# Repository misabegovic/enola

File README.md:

> **This fork is the source of munola releases.** `munola` is a distribution
> of enola built from the `current` channel of misabegovic/mu-enola, carved
> into this repository's `munola-releases-<version>` lineage: the released
> upstream plus changes that are proposed upstream, under review, or that
> upstream may never take. Releases are cut from tags `munola-v<upstream
> version>.<n>` (for example `munola-v0.4.4.1` is the first munola release on
> upstream 0.4.4), carry the same asset names as upstream with that version,
> and their notes name exactly what differs from the upstream version they
> descend from. Everything below this line is upstream's README.

<div align="center">

  <h1>enola</h1>

  <p>enola - One graph of your whole software system, built from the code, on your machine</p>

  <p align="center">
  <a href="https://enola.tech">Website</a>
  ·
  <a href="docs/README.md">Docs</a>
  ·
  <a href="docs/CLI.md">CLI reference</a>
  ·
  <a href="docs/BENCHMARKS.md">Benchmarks</a>
  ·
  <a href="https://github.com/enola-labs/enola/releases">Releases</a>
  ·
  <a href="https://github.com/enola-labs/enola/issues">Report a gap</a>
  </p>

  <p>

  </p>

  <p>enola reads your source code and writes down what is in it: the modules, the functions, the API routes, the database tables it touches, the message topics it publishes. Then it records how each of those pieces connects to the others, inside one repository and across several. That record is a <em>graph</em>: a list of things, and a list of links between them. You can ask the graph questions, hand it to your coding agent, or build your own tools on it.</p>

  <p><strong>Runs locally as one binary. No AI model, no language server, no account, no upload.</strong><br />
  The graph comes from parsing your code. The same code always produces the same graph.</p>

</div>

## When to use enola

- **Find out what a change will break.** Before you edit a function, a route, or a module, ask the graph what depends on it. The answer is a list of real places in the code, not a guess. [Quickstart](#quickstart).
- **Keep your architecture the way you declared it.** Write down the layer order your code should follow, or which service may call which. Every change is then graded against that, and only what the change broke is reported. [Grade a change](#grade-a-change).
- **Give your coding agent the structure of the system.** Over MCP, the agent asks the graph what depends on the code it is about to touch, and a hook grades its edit when it is done. [Connect your agent](#connect-your-agent).
- **See several repositories as one system.** A frontend's call to `/api/orders` is linked to the Go handler that serves it. One service's Kafka producer is linked to the service that consumes the topic. [Across repositories](#across-repositories).
- **Build your own tools on the graph.** A snapshot is a set of plain files with a documented format. Load them wherever you need them. [Build on the graph](#build-on-the-graph).

That difference shows up in ordinary work. Across 238 real Claude Code and OpenCode sessions, 4,375 enola calls put 4.1 million tokens into context. Opening only the files named in those answers was estimated at 5.4× to 7.7× as much; reading the full source represented by each session, 450× to 623×. In 205 of 210 sessions that took a snapshot, that source was larger than the agent's median active context. [Measured latency, token costs, method and limits](docs/BENCHMARKS.md#real-session-usage).

## Choose your starting point

| I want to… | Start here |
| --- | --- |
| See what enola finds in a repository I have | [Quickstart](#quickstart) |
| Check whether a change broke the architecture | [Grade a change](#grade-a-change) |
| Run that check on every pull request | [Use it in CI](#use-it-in-ci) |
| Give my coding agent the graph | [Connect your agent](#connect-your-agent) |
| Link a backend and the apps that call it | [Across repositories](#across-repositories) |
| Load the graph into my own tool | [Build on the graph](#build-on-the-graph) |
| Know which languages it understands | [What it reads](#what-it-reads) |
| Follow one worked example end to end | [Your first graded change](docs/FIRST-CHANGE.md) |

## Quickstart

**1. Install enola.** One prebuilt binary; no Go toolchain or C compiler needed.

```bash
curl -fsSL https://raw.githubusercontent.com/enola-labs/enola/main/install.sh | sh
```

This puts `enola` in `~/.local/bin`. The same binary is on PyPI (`pip install enola-cli`) and RubyGems. Every install route, and how to upgrade, is in [docs/CLI.md](docs/CLI.md#install).

**2. Point it at a repository you have checked out.**

```bash
enola --explain /path/to/your/repo
```

No config file, no account, nothing written to disk. It reads the code and prints what it found. If you have nothing at hand, run it on enola itself:

```bash
git clone https://github.com/enola-labs/enola
enola --explain enola
```

Part of what that prints (the numbers move as the code does):

```
Overview
  Languages:           go, typescript, c, ruby, python
  Total facts:         10814

Architecture
  cyclic dependencies         0
  layer violations            0

Impact analysis (hotspots)
  Top hotspots (by coupling):
    module                            fan-in  fan-out crit     blast radius
    internal/facts                       253        1 high     96
    pkg/command                            1       94 high     1
    pkg/bootstrap                         15       69 high     4
```

How to read it:

- A **fact** is one thing enola recorded: "this function exists", "this function calls that one", "this route is served here". `Total facts` is how many it found.
- A **cyclic dependency** is two or more modules that each need the other, so neither can be changed or tested alone.
- A **layer violation** is a module reaching into a layer it is not allowed to use, under a layer order the repository declared. enola declares its own in [`enola-intent.yaml`](enola-intent.yaml); 0 means nothing in the code crosses it.
- A **hotspot** is a module many other modules depend on. `fan-in` is how many modules use it; `fan-out` is how many it uses; `blast radius` is how many modules a change to it can reach. Read the first row as: `internal/facts` is used from 253 places, and a change to it can reach 96 modules.

**3. Keep the graph and look at it.** `--explain` only prints. To save the graph, build it with `--generate`. It is written under `.enola/` in the repository, and that saved graph is what the local dashboard shows:

```bash
enola --generate .
enola dashboard --open
```

The dashboard is a local web page; nothing is sent anywhere. [Dashboard guide](docs/DASHBOARD.md).

## How enola works

enola parses each source file, turns what it finds into typed facts, links the facts into a graph, and runs checks over the graph: dependency cycles, layer violations, unused routes, hotspots and more. Each check is called an **explainer**, and [docs/EXPLAINERS.md](docs/EXPLAINERS.md) describes every one of them.

| Command | What it does | Learn more |
| --- | --- | --- |
| `enola --explain <repo>` | Read a repository and print a report. Writes nothing. | [CLI reference](docs/CLI.md#explain-a-repository-at-a-glance) |
| `enola --generate <repo>` | Build the graph and save it under `.enola/` as a snapshot. | [The graph](docs/GRAPH.md) |
| `enola baseline pin` | Record the current state of the graph as the point to compare against. | [Gating a change](docs/GATING.md) |
| `enola check` | Build the graph again and report only what changed since the pin. | [Gating a change](docs/GATING.md) |
| `enola coverage <cluster>` | For several repositories, say which cross-repository calls were linked and which could not be. | [Clusters](docs/CLUSTERS.md) |
| `enola dashboard --open` | Show the saved graph in a local web page. | [Dashboard guide](docs/DASHBOARD.md) |
| `enola install --hooks` | Tell your coding agents enola exists and grade each of their sessions. | [Connect your agent](#connect-your-agent) |

Three properties hold for all of it:

- **Deterministic.** The same code always gives the same graph. 91 open-source repositories indexed three times each (once cold, twice warm) gave byte-identical results, over 8.1 million facts. Every snapshot carries a **receipt**: a record of exactly how it was built. enola refuses to compare two snapshots that were not built the same way.
- **Fast enough for every commit.** Re-indexing an unchanged tree took 4.8s for grafana and 41.5s for the Linux kernel.
- **Local.** One binary reading local files. No model, no embeddings, no upload.

What the graph contains and what it writes to disk: [docs/GRAPH.md](docs/GRAPH.md). The numbers above and the scripts that produce them: [docs/BENCHMARKS.md](docs/BENCHMARKS.md). Internals: [ARCHITECTURE.md](ARCHITECTURE.md).

## Grade a change

The simplest way to see what changed is to check what came in with a pull. Record the current state, pull, and compare:

```bash
enola baseline pin
git pull
enola check
```

`enola check` builds the graph again and reports only what changed since the pin: new dependencies, new calls, new findings. Problems the repository already had stay out of the report. Your own edits work the same way: pin, change, check.

Here a new helper in `storage` imports the delivery layer. It compiles, every test passes, and it breaks the layer order the repository declared:

```
FAIL — 1 structural regression introduced.

Regressions (fail):
  - [layers] 1.00 — Layer violation: storage -> delivery
      import of notify
```

A **regression** is something the change made worse compared with the pin. Some checks grade against how you say your system should look, such as a layer order or which service may call which. You write that down in [docs/INTENT.md](docs/INTENT.md) and [docs/CONSTRAINTS.md](docs/CONSTRAINTS.md).

Nothing fails by default. You choose what should, for example `enola check --fail-on=layers`. [docs/GATING.md](docs/GATING.md) explains what can fail a build and why; [docs/HISTORY.md](docs/HISTORY.md) covers how the architecture changed over time. The whole loop on a module small enough to read in a minute: [docs/FIRST-CHANGE.md](docs/FIRST-CHANGE.md).

## Use it in CI

The same check runs on every pull request with [enola-action](https://github.com/enola-labs/enola-action). It resolves the exact base commit, grades both sides on the runner, annotates the lines that introduced a finding, and writes the architecture delta to the job summary:

```yaml
- uses: actions/checkout@v7
  with:
    fetch-depth: 0
- uses: enola-labs/enola-action@v2   # reports only; add fail-on to gate
```

Same explainers and same exit codes as `enola check` in your shell, with no baseline to publish or restore. A ready workflow file is in [`examples/ci/`](examples/ci/).

## Connect your agent

First tell your agents enola exists, and let it grade each session:

```bash
enola install --hooks
```

Then give the agent the graph over **MCP** (Model Context Protocol: the standard way a coding agent calls an outside tool):

| Client | Do this |
|---|---|
| **Claude Code** | `claude mcp add enola enola` |
| **Codex** | `codex mcp add enola -- enola` |
| **Copilot (VS Code)** | `code --add-mcp '{"name":"enola","command":"enola"}'` |
| **Cursor** | add the block below to `.cursor/mcp.json` (or `~/.cursor/mcp.json` for every project) |
| **opencode** | nothing, `enola install` already registered it |
| **Pi** | nothing, `enola install` wrote an extension that serves the tools (Pi has no MCP client); trust the project in Pi, or use `--global` |
| **Any other MCP client** | add the block below to its MCP config |

```json
{ "mcpServers": { "enola": { "command": "enola" } } }
```

What changes for the agent: before an edit, it asks the graph what depends on the code it is about to touch, instead of piecing that together from text searches. After the edit, a **hook** (a command the agent runs automatically at the end of its turn) runs the same `enola check` as above. The agent sees what it actually changed and fixes a regression before telling you it is done.

`enola install` previews every file it changes and asks first; `enola uninstall` reverses all of it. `enola doctor` tells you whether the hooks are really firing. Per-client details, including Copilot's different config key: [docs/CLI.md](docs/CLI.md#connect-it-to-your-agent).

## Across repositories

A system rarely lives in one repository, so enola does not stop at one. Give it a backend and the things that call it (a web app, a mobile app, another service) and it links them into one graph. Then it can answer: *if I change this endpoint, what breaks?*

The hard part is that two sides rarely spell an endpoint the same way. In [`examples/cross-repo/`](examples/cross-repo/) the web service calls `/api/v2/orders/{id}`, but the API service never writes that string anywhere:

```go
v2 := r.PathPrefix("/api/v2").Subrouter()
registerOrders(v2)                        // in main()

r.HandleFunc("/orders/{id}", getOrder)    // in registerOrders(), a different function
```

enola follows the prefix into the function it was passed to and files the route under the address it actually answers on, so the call links. It does the same for Express, FastAPI, Axum, Rails and Swift, where the prefix often sits in another file entirely.

When it *cannot* link something, it says so instead of guessing:

```
$ enola coverage cluster.yaml

  service  classification  detected  resolved  unresolved
  api      isolated              0         0           0
  web      connected             3         2           1
```

The unresolved call builds its URL at runtime, so there is nothing to match. That distinction matters: a service with no connections and a service whose connections enola failed to follow should never look the same. The example runs in one command: `./run.sh`. How several repositories are described and matched: [docs/CLUSTERS.md](docs/CLUSTERS.md).

## Build on the graph

A **snapshot** is a set of plain files with a [documented format](docs/schema/README.md): the facts, the relationships between them, the findings, and a receipt recording exactly how it was built. Run enola as a subprocess and load those files wherever you need them.

[Cognee](https://github.com/topoteretes/cognee) builds its code-graph search this way: it pins an `enola-cli` release and loads the snapshot files, and that search needs no LLM key. How it finds the binary and what it writes: [docs/INTEGRATING.md](docs/INTEGRATING.md#cognee). If you got enola as part of Cognee, [docs/COGNEE.md](docs/COGNEE.md) shows where the binary is and how to use it directly.

[docs/GRAPH.md](docs/GRAPH.md) explains what the graph contains and which files are a stable contract; [docs/INTEGRATING.md](docs/INTEGRATING.md) shows how to load it step by step.

## What it reads

More than twenty languages and formats, detected automatically. A repository with two languages is indexed as two languages without being told.

- **Application code:** Go, Java, Kotlin, Scala, JavaScript, TypeScript, Vue, Svelte, Ember, Angular, Python, Ruby, PHP, Swift, Dart/Flutter, Rust, C/C++, .NET (C#, VB.NET, F#)
- **APIs and messaging:** OpenAPI, gRPC, GraphQL, AsyncAPI
- **Infrastructure:** Terraform/HCL, Ansible

On top of the language it understands the frameworks that shape routes, storage and wiring, among them Rails, Django, FastAPI, Spring, Express, Next.js, ASP.NET Core, Laravel, Axum, SwiftUI and Jetpack Compose. The full table is in [docs/LANGUAGES.md](docs/LANGUAGES.md). A language you do not see there is a gap worth [reporting](https://github.com/enola-labs/enola/issues).

## Explore examples

Each example is a small repository plus a `run.sh` that reproduces the output shown in its README.

- [The gate on five packages](examples/layers-gate/): a module built to a layer order, and one change that breaks it. This is the fixture the outputs in this README come from.
- [Two repositories, one graph](examples/cross-repo/): a web service and the API it calls, with one call enola can link and one it reports as unresolved.
- [Policy as code](examples/policy-as-code/): PCI DSS and GDPR-inspired constraints on a small Go module, with three changes that violate them.
- [A custom HTTP client](examples/custom-client/): teaching enola an in-house client so its calls link to server routes.
- [A CI workflow](examples/ci/) and [a pre-commit hook](examples/hooks/) ready to copy.
- [Per-language configuration files](examples/) for Go, TypeScript, Python, Ruby, PHP, Kotlin, Swift and C++.

## Benchmarks

Every number below is measured on public repositories with scripts you can rerun. Method, corpus and limits: [docs/BENCHMARKS.md](docs/BENCHMARKS.md).

| Question | Result | What was measured |
| --- | --- | --- |
| Does the same commit produce the same graph? | **91 / 91** | public repositories produced byte-identical graphs across a cold run and two warm ones |
| When something regresses, is exactly that reported? | **20 / 20** | injected dependency cycles caught, with none of 1,859 pre-existing findings repeated as new |
| Of the cross-repository calls that exist, how many are linked? | **19 / 24** | fixture calls resolved, with the 3 unresolved and 2 external ones reported, not hidden |
| Does it finish on a real repository? | **0** | parse errors across the whole corpus, the Linux kernel included |
| Does an agent, given the check, avoid shipping the regression? | **3 / 3 → 0 / 3** | agents shipped the injected cycle without enola, and none did with the hooks installed |

## Limitations

- enola models structure, not runtime behaviour. It knows a service calls another; it knows nothing about timeouts, retries or whether a message can be lost.
- Calls it cannot resolve, such as URLs built at runtime, are reported as unresolved rather than guessed. Per-language limits are in [docs/extraction/](docs/extraction/) and the gaps found so far in [docs/BLIND-SPOTS.md](docs/BLIND-SPOTS.md).
- Most findings are advisory. Across the benchmark corpus, 89.2% of them could not fail a build even with every check named.
- A clean `enola check` means the change introduced nothing new, not that the repository is clean.

With a coding agent, most of these stop being dead ends. enola says exactly where its knowledge stops: which call it could not resolve, which finding is only advisory. The agent can open that file, read the retry settings or the URL being built, and judge whether a finding matters for this change. The graph shows the agent where to look; the agent reads what the graph cannot hold. What the agent concludes is still the agent's judgement, not a measurement, and enola keeps the two apart.

## Documentation

- **[Choose a guide by task](docs/README.md)**
- **[Your first graded change](docs/FIRST-CHANGE.md)**: the loop end to end, on a module small enough to read
- **[The graph](docs/GRAPH.md)**: what is in it, how it is built, what it writes to disk
- **[CLI reference](docs/CLI.md)**: install, agent setup, commands, flags and exit codes
- **[Gating a change](docs/GATING.md)**: what a verdict contains and what can fail a build
- **[Dashboard guide](docs/DASHBOARD.md)**
- **[Building on enola](docs/INTEGRATING.md)**
- **[Glossary](docs/GLOSSARY.md)**: the terms used in enola's output
- **[Architecture](ARCHITECTURE.md)**: the fact model, pipeline, graph and MCP tools
- **[Changelog](CHANGELOG.md)** and **[examples](examples/)**

## Community & Support

### Found it useful?

If `enola --explain` told you something about your codebase you did not already know, a star helps other people find it.

If it missed something it should have caught (an unresolved edge, a route it did not match, a construct it walked past), please [open an issue](https://github.com/enola-labs/enola/issues). Those are the most useful bug reports this project gets.

### Contributing

Code, documentation, bug reports and feature ideas are all welcome. [`CONTRIBUTING.md`](CONTRIBUTING.md) covers the development workflow, the architecture gate that runs on every pull request, and how to add a language, a connection or an analysis.

### Code of Conduct

Read the [Code of Conduct](CODE_OF_CONDUCT.md) for the guidelines this community follows.

## License

Apache License 2.0, see [`LICENSE`](LICENSE).

This repository is the full engine, not a trial edition. Nothing is gated, metered or degraded without a key, and no snapshot, fact or usage counter ever leaves your machine. The only outbound request enola makes is to GitHub's release API: a background release check you can turn off (see [Staying current](docs/CLI.md#staying-current)), and `enola upgrade` when you run it.

## Acknowledgements

**[Muhamed Isabegović](https://github.com/misabegovic)** is the author of a large part of
what this repository does. The constraints program — declared architectural law over the
fact graph — is his, along with the vocabulary it verdicts, `plan` and `constraints mine`,
the fact-provider seam and the providers that ride it, the shareable history store behind
`blame` and `diff`, declared intent compiling into the graph, Ember support, the Rails
extraction work with the `dead-methods` and `query-loops` explainers, the Ruby surface for
writing laws as sentences, and the verdict writers that put a finding where CI reads it.
He also maintains the Ruby and Rails integration gems that drive enola from Bundler.

enola bundles third-party components under their own licenses; see [`NOTICE`](NOTICE). Swift parsing uses the [tree-sitter-swift](https://github.com/alex-pinkus/tree-sitter-swift) grammar by Alex Pinkus (MIT), vendored under [`internal/extractors/swiftextractor/grammar/`](internal/extractors/swiftextractor/grammar/); Dart parsing uses [tree-sitter-dart](https://github.com/UserNobody14/tree-sitter-dart) by UserNobody14 and others (MIT), vendored under [`internal/extractors/dartextractor/grammar/`](internal/extractors/dartextractor/grammar/); Scala parsing uses [tree-sitter-scala](https://github.com/tree-sitter/tree-sitter-scala) (MIT), vendored under [`internal/extractors/scalaextractor/grammar/`](internal/extractors/scalaextractor/grammar/); Ruby parsing uses [tree-sitter-ruby](https://github.com/tree-sitter/tree-sitter-ruby) (MIT) v0.23.1 with a patch for anonymous block forwarding, vendored under [`internal/extractors/rubyextractor/grammar/`](internal/extractors/rubyextractor/grammar/). Every other grammar is a normal Go module dependency and is not vendored.

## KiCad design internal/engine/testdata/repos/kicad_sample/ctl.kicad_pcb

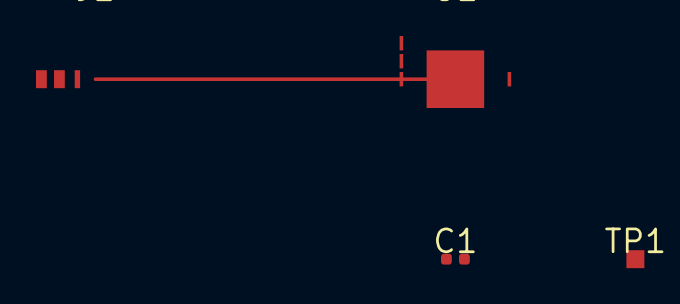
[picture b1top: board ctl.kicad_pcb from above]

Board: 0 copper layers, 5 parts (1 on the bottom side), 3 nets.

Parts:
C1: 100n; C_0402_1005Metric
J1: USB_C; USB_C_Receptacle
TP1, TP1#2: TestPoint; TestPoint_Pad_1.0x1.0mm
U1: RP2040; QFN-56-1EP_7x7mm_P0.4mm

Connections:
+3V3: C1.1, U1.1
/MCU/USB_D+: J1.A6, U1.3
GND: C1.2, J1.A1, TP1.1, TP1#2.1, U1.2, U1.57
